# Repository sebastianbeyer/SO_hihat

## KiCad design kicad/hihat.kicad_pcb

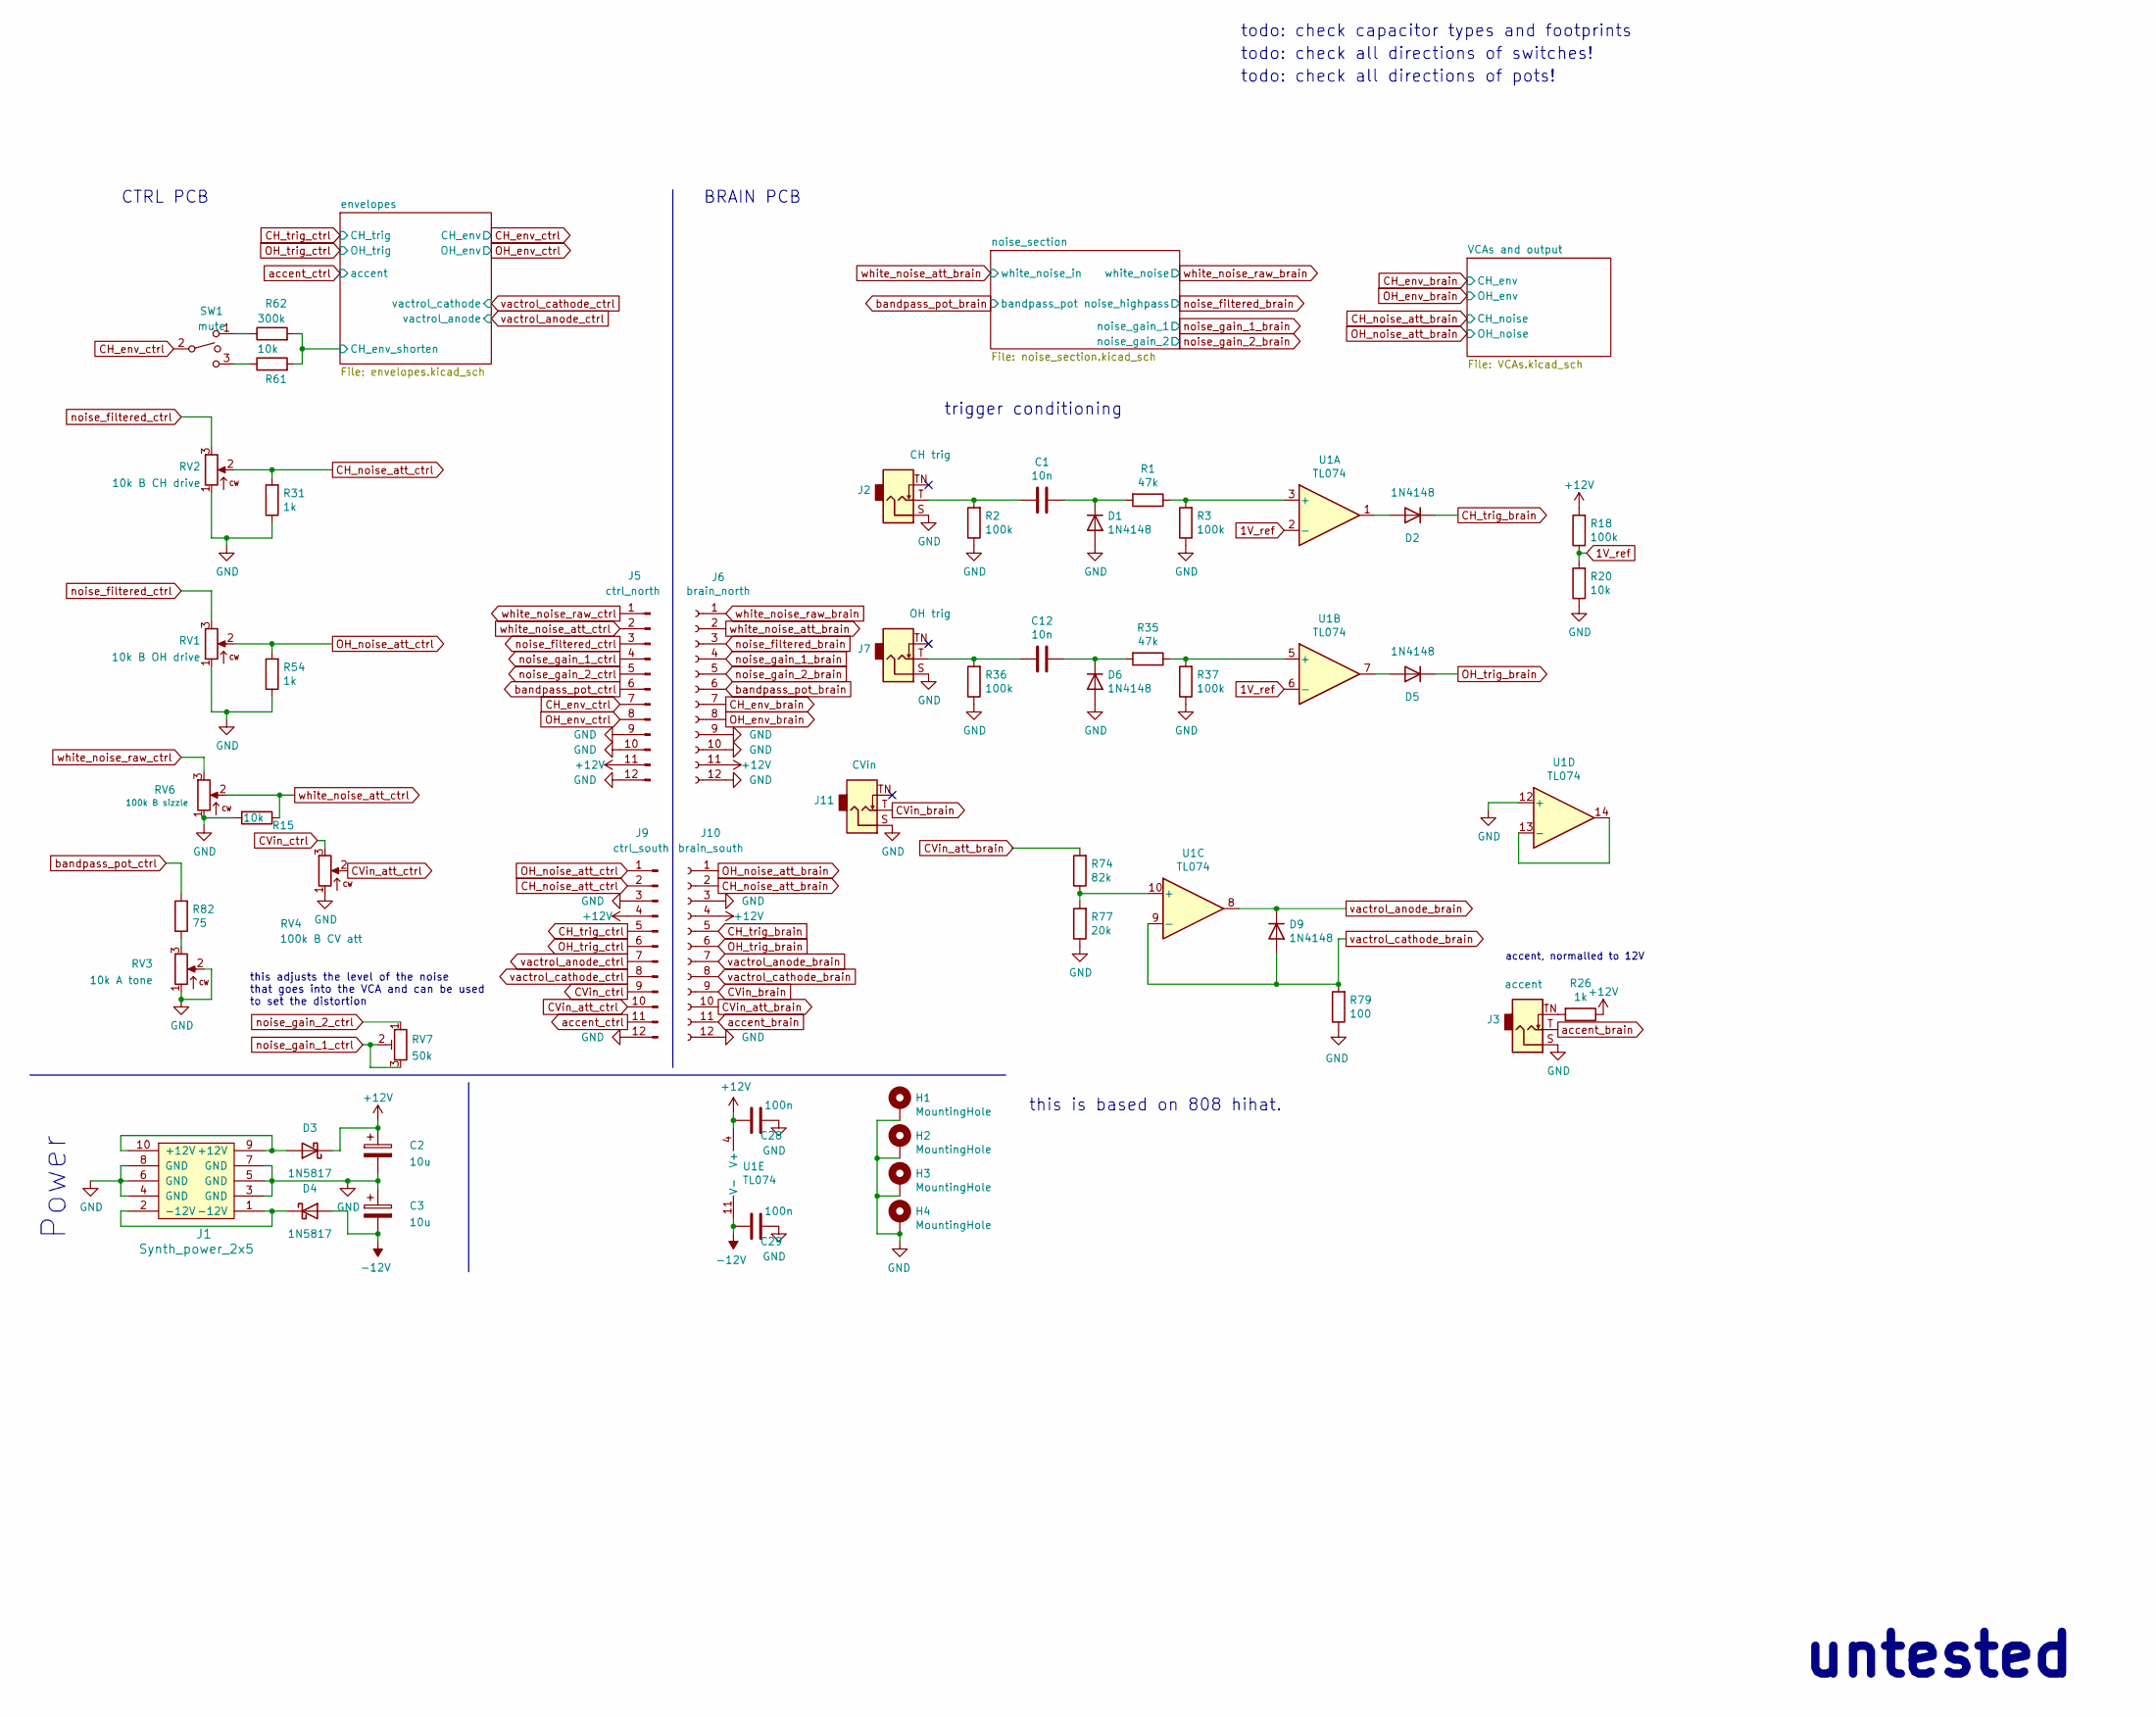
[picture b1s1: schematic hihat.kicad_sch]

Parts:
C1, C12: 10n; C_Disc_D3.0mm_W1.6mm_P2.50mm
C2, C3: 10u; CP_Radial_horizontalflat_D5mm_P2.50mm_H10mm
C28, C29: 100n; C_Disc_D3.0mm_W1.6mm_P2.50mm
D1, D2, D5, D6, D9: 1N4148; D_DO-35_SOD27_P7.62mm_Horizontal
D3, D4: 1N5817; D_DO-41_SOD81_P10.16mm_Horizontal
H1, H2, H3, H4: MountingHole; MountingHole_3.2mm_M3_Pad
J1: Synth_power_2x5; Power_Header
J2: CH trig; Jack_6.35mm_PJ_629HAN
J3: accent; Jack_6.35mm_PJ_629HAN
J5: ctrl_north; PinHeader_1x12_P2.54mm_Vertical
J6: brain_north; PinSocket_1x12_P2.54mm_Vertical
J7: OH trig; Jack_6.35mm_PJ_629HAN
J9: ctrl_south; PinHeader_1x12_P2.54mm_Vertical
J10: brain_south; PinSocket_1x12_P2.54mm_Vertical
J11: CVin; Jack_6.35mm_PJ_629HAN
R1, R35: 47k; R_Axial_DIN0207_L6.3mm_D2.5mm_P10.16mm_Horizontal
R2, R3, R18, R36, R37: 100k; R_Axial_DIN0207_L6.3mm_D2.5mm_P10.16mm_Horizontal
R15, R20, R61: 10k; R_Axial_DIN0207_L6.3mm_D2.5mm_P10.16mm_Horizontal
R26, R31, R54: 1k; R_Axial_DIN0207_L6.3mm_D2.5mm_P10.16mm_Horizontal
R62: 300k; R_Axial_DIN0207_L6.3mm_D2.5mm_P10.16mm_Horizontal
R74: 82k; R_Axial_DIN0207_L6.3mm_D2.5mm_P10.16mm_Horizontal
R77: 20k; R_Axial_DIN0207_L6.3mm_D2.5mm_P10.16mm_Horizontal
R79: 100; R_Axial_DIN0207_L6.3mm_D2.5mm_P10.16mm_Horizontal
R82: 75; R_Axial_DIN0207_L6.3mm_D2.5mm_P10.16mm_Horizontal
RV1: 10k B OH drive; Potentiometer_Alpha_RD901F-40-00D_Single_Vertical_centered
RV2: 10k B CH drive; Potentiometer_Alpha_RD901F-40-00D_Single_Vertical_centered
RV3: 10k A tone; Potentiometer_Alpha_RD901F-40-00D_Single_Vertical_centered
RV4: 100k B CV att; Potentiometer_Alpha_RD901F-40-00D_Single_Vertical_centered
RV6: 100k B sizzle; Potentiometer_Alpha_RD901F-40-00D_Single_Vertical_centered
RV7: 50k; Potentiometer_Bourns_3296W_Vertical_standard
SW1: mute; SPDT-toggle-switch-1M-series
U1: TL074; DIP-14_W7.62mm_Socket_LongPads

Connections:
1V_ref: R18.1, R20.2, U1.2 (-), U1.6 (-)
+12V: C2.1, C28.2, D3.1 (K), J5.11, J6.11, J9.4, J10.4, R18.2, R26.1, U1.4 (V+); also elsewhere on the board
-12V: C3.2, C29.2, D4.2 (A), U1.11 (V-); also elsewhere on the board
/envelopes/CH_env_shorten: R61.2, R62.2; also elsewhere on the board
CH_env_brain: J6.7; also elsewhere on the board
CH_env_ctrl: J5.7, SW1.2; also elsewhere on the board
CH_noise_att_brain: J10.2; also elsewhere on the board
CH_noise_att_ctrl: J9.2, R31.2, RV2.2
CH_trig_brain: D2.1 (K), J10.5
CH_trig_ctrl: J9.5; also elsewhere on the board
CVin_att_brain: J10.10, R74.2
CVin_att_ctrl: J9.10, RV4.2
CVin_brain: J10.9, J11.T
CVin_ctrl: J9.9, RV4.3
GND: C2.2, C3.1, C28.1, C29.1, D1.2 (A), D6.2 (A), H1.1, H2.1, H3.1, H4.1, J1.3 (GND), J1.4 (GND), J1.5 (GND), J1.6 (GND), J1.7 (GND), J1.8 (GND), J2.S, J3.S, J5.9, J5.10, J5.12, J6.9, J6.10, J6.12, J7.S, J9.3, J9.12, J10.3, J10.12, J11.S, R2.1, R3.1, R15.2, R20.1, R31.1, R36.1, R37.1, R54.1, R77.1, R79.1, RV1.1, RV2.1, RV3.1, RV3.2, RV4.1, RV6.1, U1.12 (+); also elsewhere on the board
unnamed: C1.1, D1.1 (K), R1.2
unnamed: C1.2, J2.T, R2.2
unnamed: C12.1, D6.1 (K), R35.2
unnamed: C12.2, J7.T, R36.2
unnamed: D2.2 (A), U1.1
unnamed: D3.2 (A), J1.9 (+12V), J1.10 (+12V)
unnamed: D4.1 (K), J1.1 (-12V), J1.2 (-12V)
unnamed: D5.2 (A), U1.7
unnamed: J3.TN, R26.2
unnamed: R1.1, R3.2, U1.3 (+)
unnamed: R35.1, R37.2, U1.5 (+)
unnamed: R61.1, SW1.3
unnamed: R62.1, SW1.1
unnamed: R74.1, R77.2, U1.10 (+)
unnamed: R82.1, RV3.3
unnamed: U1.13 (-), U1.14
OH_env_brain: J6.8; also elsewhere on the board
OH_env_ctrl: J5.8; also elsewhere on the board
OH_noise_att_brain: J10.1; also elsewhere on the board
OH_noise_att_ctrl: J9.1, R54.2, RV1.2
OH_trig_brain: D5.1 (K), J10.6
OH_trig_ctrl: J9.6; also elsewhere on the board
accent_brain: J3.T, J10.11
accent_ctrl: J9.11; also elsewhere on the board
bandpass_pot_brain: J6.6; also elsewhere on the board
bandpass_pot_ctrl: J5.6, R82.2
noise_filtered_brain: J6.3, J6.5; also elsewhere on the board
noise_filtered_ctrl: J5.3, RV1.3, RV2.3
noise_gain_1_brain: J6.4; also elsewhere on the board
noise_gain_1_ctrl: J5.4, RV7.2, RV7.3
noise_gain_2_ctrl: J5.5, RV7.1
vactrol_anode_brain: D9.1 (K), J10.7, U1.8
vactrol_anode_ctrl: J9.7; also elsewhere on the board
vactrol_cathode_brain: D9.2 (A), J10.8, R79.2, U1.9 (-)
vactrol_cathode_ctrl: J9.8; also elsewhere on the board
white_noise_att_brain: J6.2; also elsewhere on the board
white_noise_att_ctrl: J5.2, R15.1, RV6.2
white_noise_raw_brain: J6.1; also elsewhere on the board
white_noise_raw_ctrl: J5.1, RV6.3

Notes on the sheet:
untested
trigger conditioning
CTRL PCB
accent, normalled to 12V
todo: check all directions of switches!
this is based on 808 hihat.
Power
todo: check capacitor types and footprints
todo: check all directions of pots!
this adjusts the level of the noise that goes into the VCA and can be used to set the distortion
BRAIN PCB

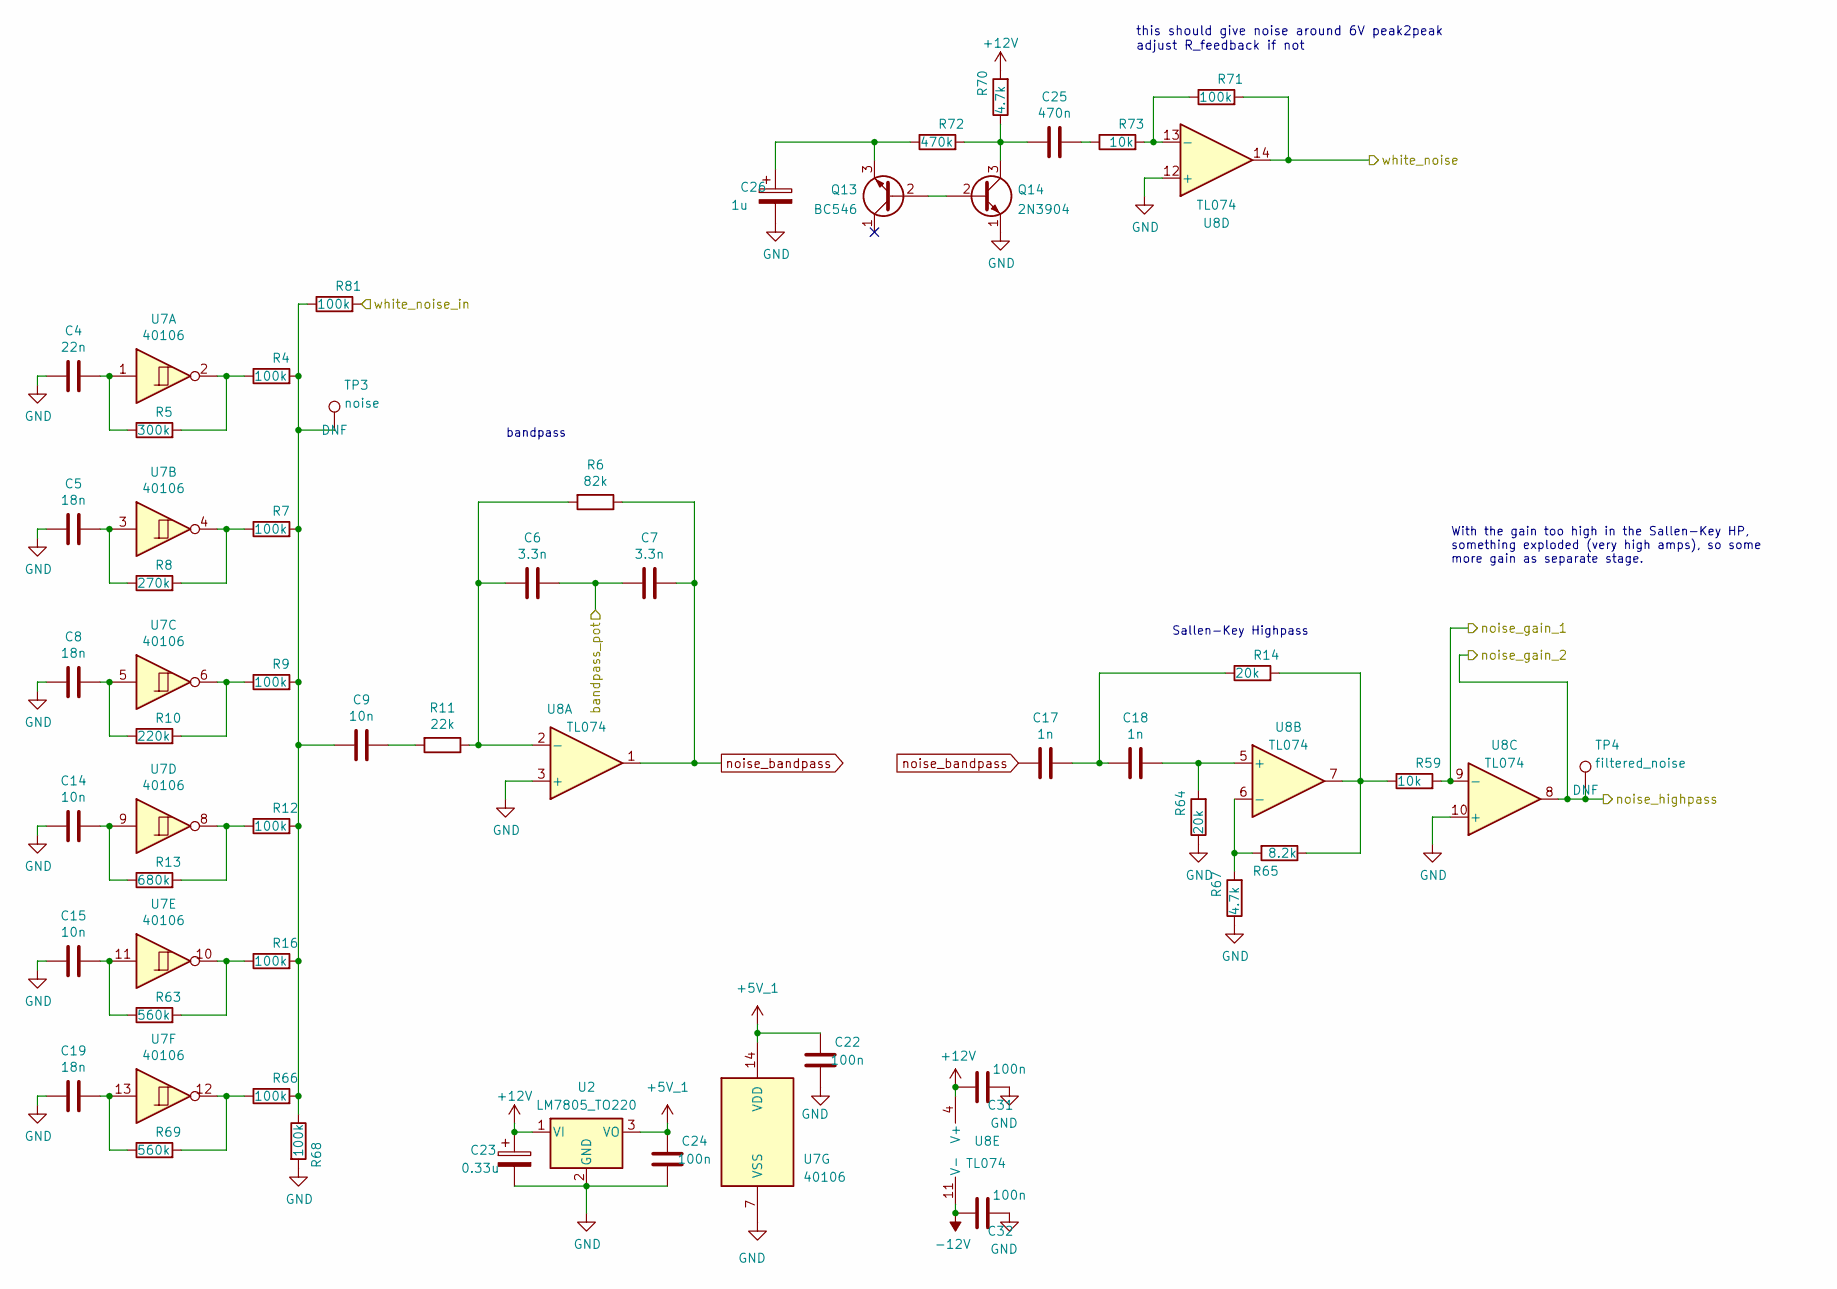
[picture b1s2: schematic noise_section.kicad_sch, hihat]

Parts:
C4: 22n; C_Rect_L7.2mm_W2.5mm_P5.00mm_FKS2_FKP2_MKS2_MKP2
C5, C8, C19: 18n; C_Rect_L7.2mm_W2.5mm_P5.00mm_FKS2_FKP2_MKS2_MKP2
C6, C7: 3.3n; C_Rect_L7.2mm_W2.5mm_P5.00mm_FKS2_FKP2_MKS2_MKP2
C9, C14, C15: 10n; C_Rect_L7.2mm_W2.5mm_P5.00mm_FKS2_FKP2_MKS2_MKP2
C17, C18: 1n; C_Rect_L7.2mm_W2.5mm_P5.00mm_FKS2_FKP2_MKS2_MKP2
C22, C24, C31, C32: 100n; C_Disc_D3.0mm_W1.6mm_P2.50mm
C23: 0.33u; CP_Radial_horizontalflat_D5mm_P2.50mm_H10mm
C25: 470n; C_Rect_L7.2mm_W2.5mm_P5.00mm_FKS2_FKP2_MKS2_MKP2
C26: 1u; CP_Radial_horizontalflat_D5mm_P2.50mm_H10mm
Q13: BC546; TO-92_Inline_Wide
Q14: 2N3904; TO-92_Inline_Wide
R4, R7, R9, R12, R16, R66, R68, R71, R81: 100k; R_Axial_DIN0207_L6.3mm_D2.5mm_P10.16mm_Horizontal
R5: 300k; R_Axial_DIN0207_L6.3mm_D2.5mm_P10.16mm_Horizontal
R6: 82k; R_Axial_DIN0207_L6.3mm_D2.5mm_P10.16mm_Horizontal
R8: 270k; R_Axial_DIN0207_L6.3mm_D2.5mm_P10.16mm_Horizontal
R10: 220k; R_Axial_DIN0207_L6.3mm_D2.5mm_P10.16mm_Horizontal
R11: 22k; R_Axial_DIN0207_L6.3mm_D2.5mm_P10.16mm_Horizontal
R13: 680k; R_Axial_DIN0207_L6.3mm_D2.5mm_P10.16mm_Horizontal
R14, R64: 20k; R_Axial_DIN0207_L6.3mm_D2.5mm_P10.16mm_Horizontal
R59, R73: 10k; R_Axial_DIN0207_L6.3mm_D2.5mm_P10.16mm_Horizontal
R63, R69: 560k; R_Axial_DIN0207_L6.3mm_D2.5mm_P10.16mm_Horizontal
R65: 8.2k; R_Axial_DIN0207_L6.3mm_D2.5mm_P10.16mm_Horizontal
R67, R70: 4.7k; R_Axial_DIN0207_L6.3mm_D2.5mm_P10.16mm_Horizontal
R72: 470k; R_Axial_DIN0207_L6.3mm_D2.5mm_P10.16mm_Horizontal
TP3: noise; TestPoint_THTPad_D1.5mm_Drill0.7mm
TP4: filtered_noise; TestPoint_THTPad_D1.5mm_Drill0.7mm
U2: LM7805_TO220; TO-220-3_Horizontal_TabDown
U7: 40106; DIP-14_W7.62mm_Socket_LongPads
U8: TL074; DIP-14_W7.62mm_Socket_LongPads

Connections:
+5V_1: C22.1, C24.1, U2.3 (VO), U7.14 (VDD)
+12V: C23.1, C31.2, R70.2, U2.1 (VI), U8.4 (V+); also elsewhere on the board
-12V: C32.2, U8.11 (V-); also elsewhere on the board
GND: C4.2, C5.2, C8.2, C14.2, C15.2, C19.2, C22.2, C23.2, C24.2, C26.2, C31.1, C32.1, Q14.1 (E), R64.1, R67.1, R68.2, U2.2 (GND), U7.7 (VSS), U8.3 (+), U8.10 (+), U8.12 (+); also elsewhere on the board
unnamed: C4.1, R5.1, U7.1
unnamed: C5.1, R8.1, U7.3
unnamed: C6.2, R6.2, R11.1, U8.2 (-)
unnamed: C8.1, R10.1, U7.5
unnamed: C9.1, R11.2
unnamed: C9.2, R4.2, R7.2, R9.2, R12.2, R16.2, R66.2, R68.1, R81.1, TP3.1
unnamed: C14.1, R13.1, U7.9
unnamed: C15.1, R63.1, U7.11
unnamed: C17.1, C18.2, R14.1
unnamed: C18.1, R64.2, U8.5 (+)
unnamed: C19.1, R69.1, U7.13
unnamed: C25.1, R73.1
unnamed: C25.2, Q14.3 (C), R70.1, R72.2
unnamed: C26.1, Q13.3 (E), R72.1
unnamed: Q13.2 (B), Q14.2 (B)
unnamed: R4.1, R5.2, U7.2
unnamed: R7.1, R8.2, U7.4
unnamed: R9.1, R10.2, U7.6
unnamed: R12.1, R13.2, U7.8
unnamed: R14.2, R59.1, R65.1, U8.7
unnamed: R16.1, R63.2, U7.10
unnamed: R65.2, R67.2, U8.6 (-)
unnamed: R66.1, R69.2, U7.12
unnamed: R71.1, R73.2, U8.13 (-)
bandpass_pot_brain: C6.1, C7.2; also elsewhere on the board
noise_bandpass: C7.1, C17.2, R6.1, U8.1
noise_filtered_brain: TP4.1, U8.8; also elsewhere on the board
noise_gain_1_brain: R59.2, U8.9 (-); also elsewhere on the board
white_noise_att_brain: R81.2; also elsewhere on the board
white_noise_raw_brain: R71.2, U8.14; also elsewhere on the board

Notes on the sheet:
With the gain too high in the Sallen-Key HP, something exploded (very high amps), so some more gain as separate stage.
bandpass
this should give noise around 6V peak2peak adjust R_feedback if not
Sallen-Key Highpass

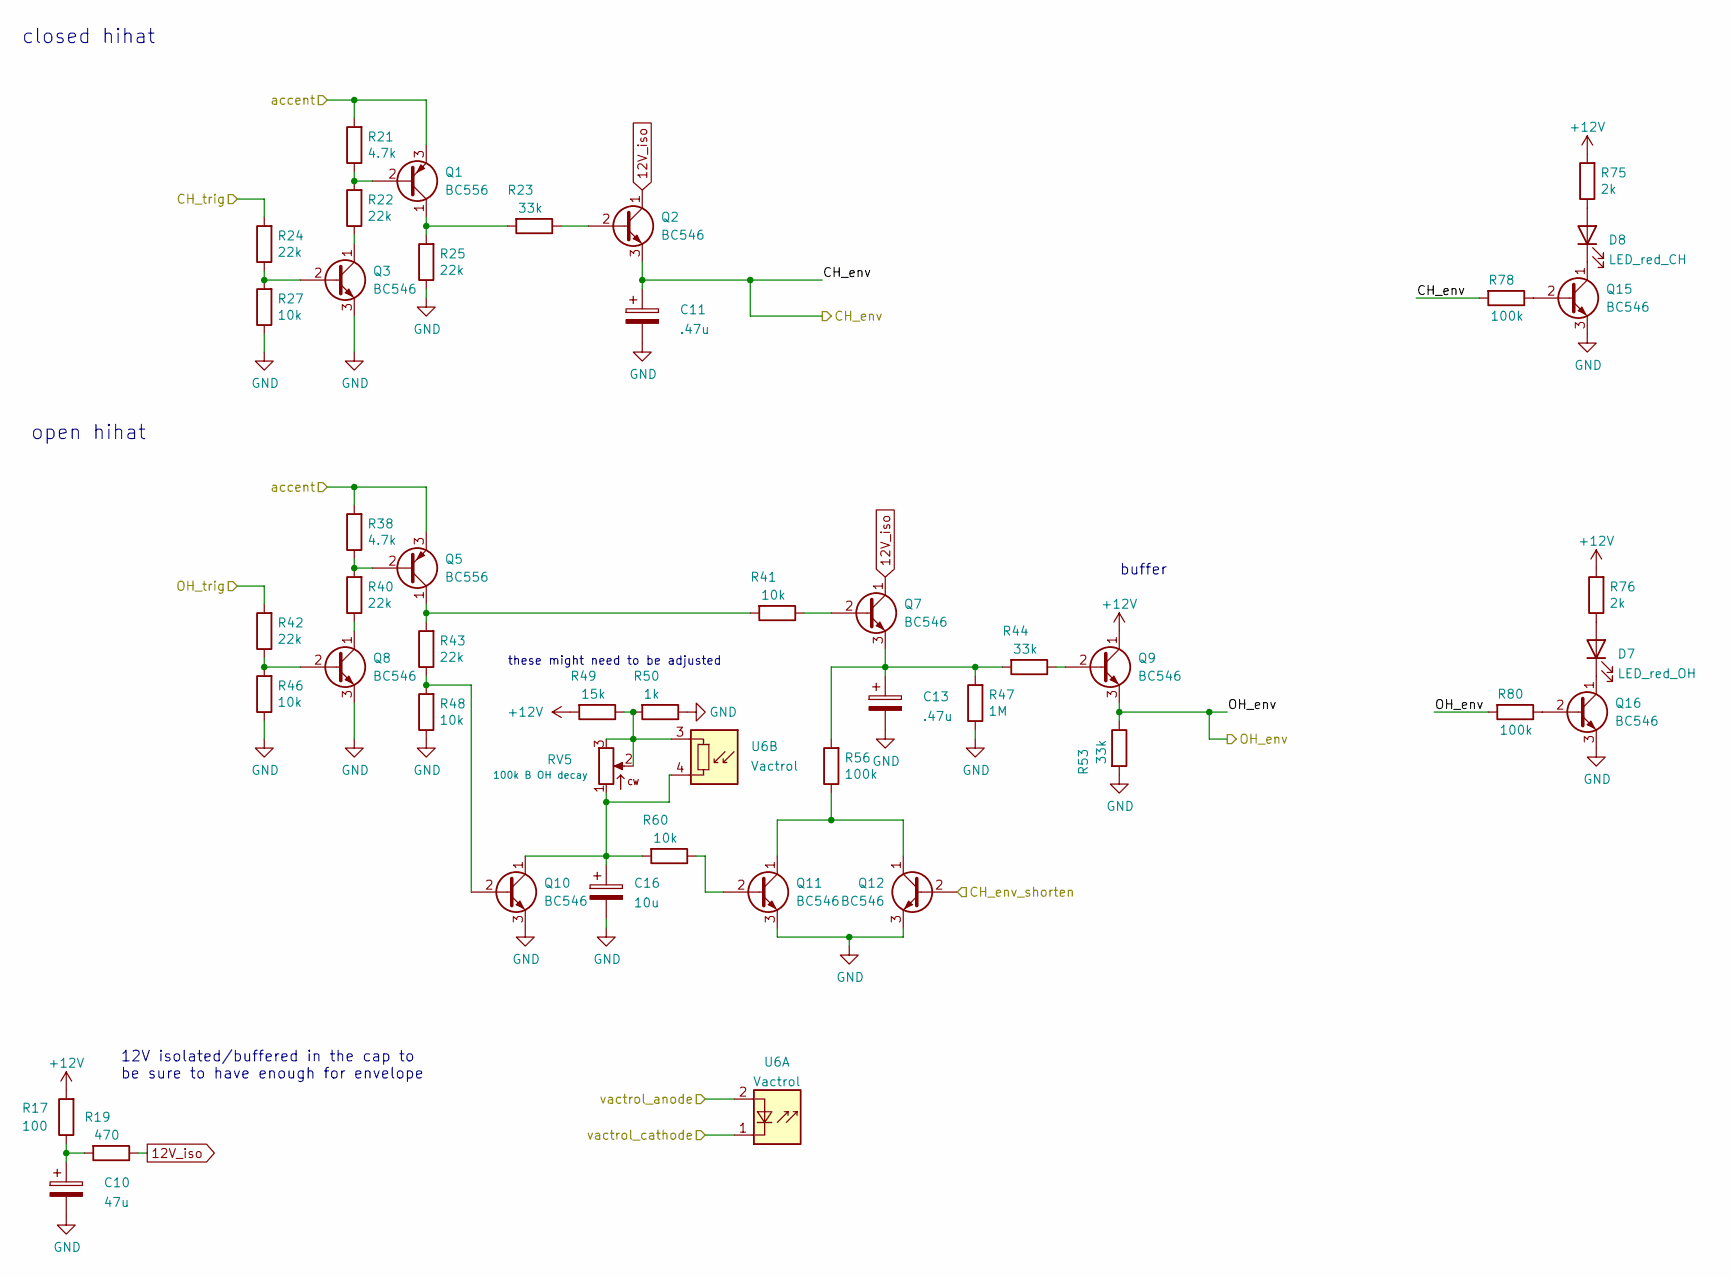
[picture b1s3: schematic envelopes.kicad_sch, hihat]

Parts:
C10: 47u; CP_Radial_horizontalflat_D5mm_P2.50mm_H10mm_south
C11, C13: .47u; CP_Radial_horizontalflat_D5mm_P2.50mm_H10mm
C16: 10u; CP_Radial_horizontalflat_D5mm_P2.50mm_H10mm
D7: LED_red_OH; LED_D5.0mm
D8: LED_red_CH; LED_D5.0mm
Q1, Q5: BC556; TO-92_Inline_Wide
Q2, Q3, Q7, Q8, Q9, Q10, Q11, Q12, Q15, Q16: BC546; TO-92_Inline_Wide
R17: 100; R_Axial_DIN0207_L6.3mm_D2.5mm_P10.16mm_Horizontal
R19: 470; R_Axial_DIN0207_L6.3mm_D2.5mm_P10.16mm_Horizontal
R21, R38: 4.7k; R_Axial_DIN0207_L6.3mm_D2.5mm_P10.16mm_Horizontal
R22, R24, R25, R40, R42, R43: 22k; R_Axial_DIN0207_L6.3mm_D2.5mm_P10.16mm_Horizontal
R23, R44, R53: 33k; R_Axial_DIN0207_L6.3mm_D2.5mm_P10.16mm_Horizontal
R27, R41, R46, R48, R60: 10k; R_Axial_DIN0207_L6.3mm_D2.5mm_P10.16mm_Horizontal
R47: 1M; R_Axial_DIN0207_L6.3mm_D2.5mm_P10.16mm_Horizontal
R49: 15k; R_Axial_DIN0207_L6.3mm_D2.5mm_P10.16mm_Horizontal
R50: 1k; R_Axial_DIN0207_L6.3mm_D2.5mm_P10.16mm_Horizontal
R56, R78, R80: 100k; R_Axial_DIN0207_L6.3mm_D2.5mm_P10.16mm_Horizontal
R75, R76: 2k; R_Axial_DIN0207_L6.3mm_D2.5mm_P10.16mm_Horizontal
RV5: 100k B OH decay; Potentiometer_Alpha_RD901F-40-00D_Single_Vertical_centered
U6: Vactrol; vactrol_Luna_NSL-32_with_diagram

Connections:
12V_iso: Q2.1 (C), Q7.1 (C), R19.1
+12V: Q9.1 (C), R17.2, R49.2, R75.2, R76.2; also elsewhere on the board
/envelopes/CH_env_shorten: Q12.2 (B); also elsewhere on the board
CH_env_ctrl: C11.1, Q2.3 (E), R78.2; also elsewhere on the board
CH_trig_ctrl: R24.2; also elsewhere on the board
GND: C10.2, C11.2, C13.2, C16.2, Q3.3 (E), Q8.3 (E), Q10.3 (E), Q11.3 (E), Q12.3 (E), Q15.3 (E), Q16.3 (E), R25.1, R27.1, R46.1, R47.1, R48.1, R50.1, R53.2; also elsewhere on the board
unnamed: C10.1, R17.1, R19.2
unnamed: C13.1, Q7.3 (E), R44.2, R47.2, R56.2
unnamed: C16.1, Q10.1 (C), R60.2, RV5.1, U6.4
unnamed: D7.1 (K), Q16.1 (C)
unnamed: D7.2 (A), R76.1
unnamed: D8.1 (K), Q15.1 (C)
unnamed: D8.2 (A), R75.1
unnamed: Q1.1 (C), R23.2, R25.2
unnamed: Q1.2 (B), R21.1, R22.2
unnamed: Q2.2 (B), R23.1
unnamed: Q3.1 (C), R22.1
unnamed: Q3.2 (B), R24.1, R27.2
unnamed: Q5.1 (C), R41.2, R43.2
unnamed: Q5.2 (B), R38.1, R40.2
unnamed: Q7.2 (B), R41.1
unnamed: Q8.1 (C), R40.1
unnamed: Q8.2 (B), R42.1, R46.2
unnamed: Q9.2 (B), R44.1
unnamed: Q10.2 (B), R43.1, R48.2
unnamed: Q11.1 (C), Q12.1 (C), R56.1
unnamed: Q11.2 (B), R60.1
unnamed: Q15.2 (B), R78.1
unnamed: Q16.2 (B), R80.1
unnamed: R49.1, R50.2, RV5.2, RV5.3, U6.3
OH_env_ctrl: Q9.3 (E), R53.1, R80.2; also elsewhere on the board
OH_trig_ctrl: R42.2; also elsewhere on the board
accent_ctrl: Q1.3 (E), Q5.3 (E), R21.2, R38.2; also elsewhere on the board
vactrol_anode_ctrl: U6.2 (+); also elsewhere on the board
vactrol_cathode_ctrl: U6.1 (-); also elsewhere on the board

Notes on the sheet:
these might need to be adjusted
open hihat
closed hihat
12V isolated/buffered in the cap to be sure to have enough for envelope
buffer

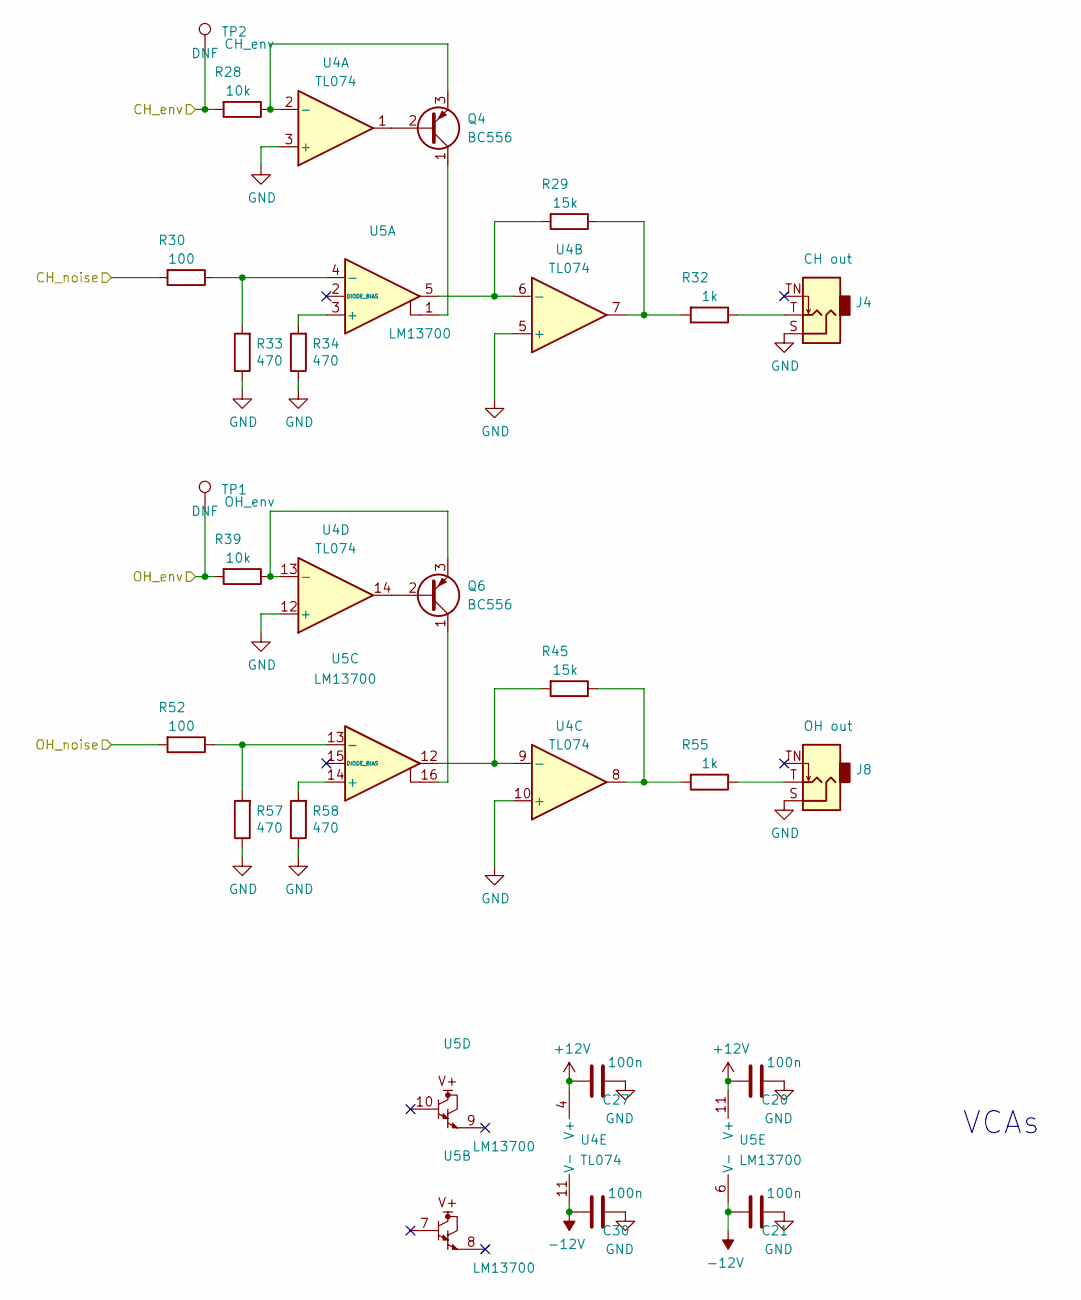
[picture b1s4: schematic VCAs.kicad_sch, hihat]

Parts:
C20, C21, C27, C30: 100n; C_Disc_D3.0mm_W1.6mm_P2.50mm
J4: CH out; Jack_6.35mm_PJ_629HAN
J8: OH out; Jack_6.35mm_PJ_629HAN
Q4, Q6: BC556; TO-92_Inline_Wide
R28, R39: 10k; R_Axial_DIN0207_L6.3mm_D2.5mm_P10.16mm_Horizontal
R29, R45: 15k; R_Axial_DIN0207_L6.3mm_D2.5mm_P10.16mm_Horizontal
R30, R52: 100; R_Axial_DIN0207_L6.3mm_D2.5mm_P10.16mm_Horizontal
R32, R55: 1k; R_Axial_DIN0207_L6.3mm_D2.5mm_P10.16mm_Horizontal
R33, R34, R57, R58: 470; R_Axial_DIN0207_L6.3mm_D2.5mm_P10.16mm_Horizontal
TP1: OH_env; TestPoint_THTPad_D1.5mm_Drill0.7mm
TP2: CH_env; TestPoint_THTPad_D1.5mm_Drill0.7mm
U4: TL074; DIP-14_W7.62mm_Socket_LongPads
U5: LM13700; DIP-16_W7.62mm_Socket_LongPads

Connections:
+12V: C20.2, C27.2, U4.4 (V+), U5.11 (V+); also elsewhere on the board
-12V: C21.2, C30.2, U4.11 (V-), U5.6 (V-); also elsewhere on the board
CH_env_brain: R28.2, TP2.1; also elsewhere on the board
CH_noise_att_brain: R30.2; also elsewhere on the board
GND: C20.1, C21.1, C27.1, C30.1, J4.S, J8.S, R33.1, R34.1, R57.1, R58.1, U4.3 (+), U4.5 (+), U4.10 (+), U4.12 (+); also elsewhere on the board
unnamed: J4.T, R32.1
unnamed: J8.T, R55.1
unnamed: Q4.1 (C), U5.1
unnamed: Q4.2 (B), U4.1
unnamed: Q4.3 (E), R28.1, U4.2 (-)
unnamed: Q6.1 (C), U5.16
unnamed: Q6.2 (B), U4.14
unnamed: Q6.3 (E), R39.1, U4.13 (-)
unnamed: R29.1, R32.2, U4.7
unnamed: R29.2, U4.6 (-), U5.5
unnamed: R30.1, R33.2, U5.4 (-)
unnamed: R34.2, U5.3 (+)
unnamed: R45.1, R55.2, U4.8
unnamed: R45.2, U4.9 (-), U5.12
unnamed: R52.1, R57.2, U5.13 (-)
unnamed: R58.2, U5.14 (+)
OH_env_brain: R39.2, TP1.1; also elsewhere on the board
OH_noise_att_brain: R52.2; also elsewhere on the board

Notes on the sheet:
VCAs
